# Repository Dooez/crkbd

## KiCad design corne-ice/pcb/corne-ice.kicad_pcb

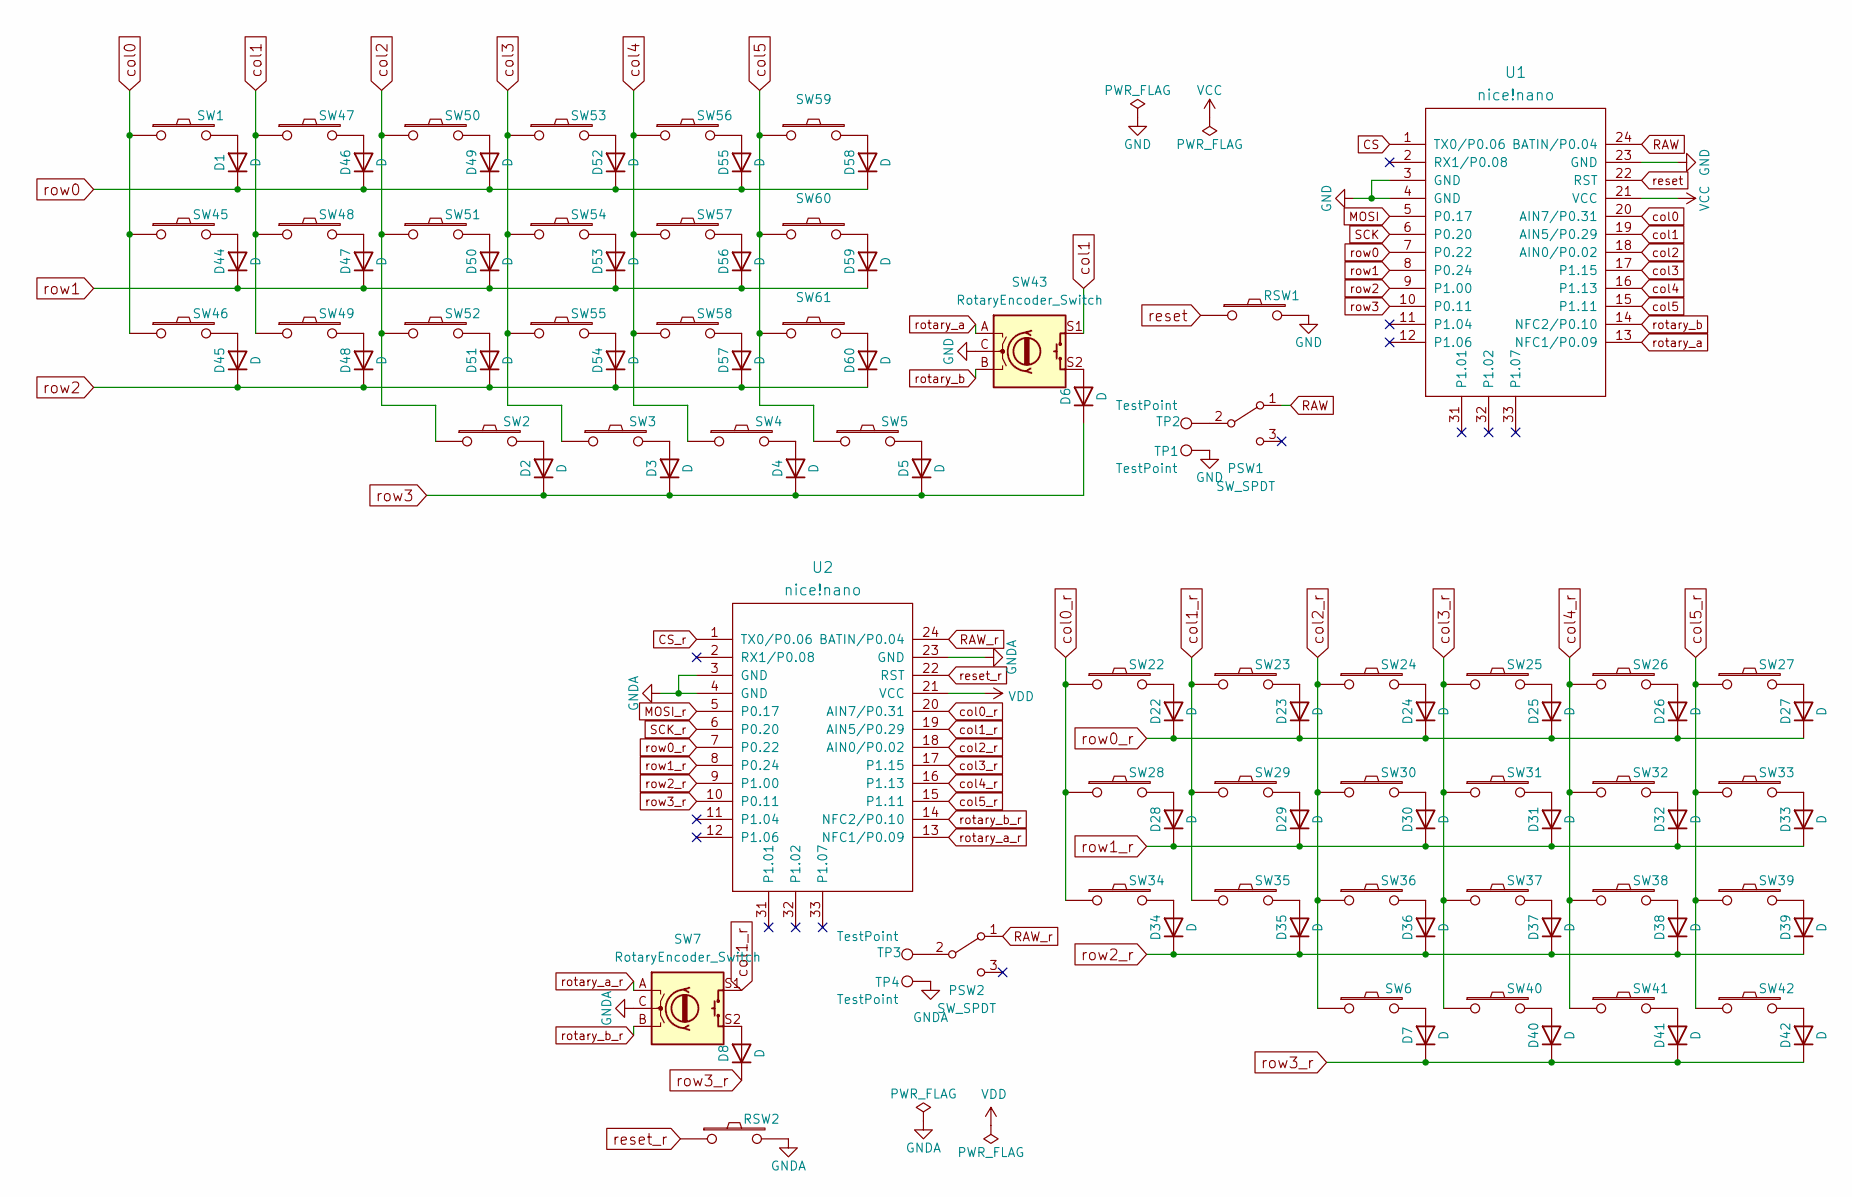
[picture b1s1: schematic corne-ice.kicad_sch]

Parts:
D1, D2, D3, D4, D5, D6, D7, D8, D22, D23, D24, D25, D26, D27, D28, D29, D30, D31, D32, D33, D34, D35, D36, D37, D38, D39, D40, D41, D42, D44, D45, D46, D47, D48, D49, D50, D51, D52, D53, D54, D55, D56, D57, D58, D59, D60: D; D3_SMD_v2
PSW1, PSW2: SW_SPDT; switch_SSSS811101
RSW1, RSW2: CPG151101S11-16; CherryMX_Hotswap
SW1, SW2, SW3, SW4, SW5, SW6, SW22, SW23, SW24, SW25, SW26, SW27, SW28, SW29, SW30, SW31, SW32, SW33, SW34, SW35, SW36, SW37, SW38, SW39, SW40, SW41, SW42, SW45, SW46, SW47, SW48, SW49, SW50, SW51, SW52, SW53, SW54, SW55, SW56, SW57, SW58, SW59, SW60, SW61: CPG151101S11-16; CherryMX_Hotswap
SW7, SW43: RotaryEncoder_Switch; RotaryEncoder_Alps_EC11E-Switch_Vertical_H20mm
TP1, TP4: TestPoint; TestPoint_Pad_1.5x1.5mm
TP2, TP3: TestPoint; TestPoint_Pad_D1.5mm
U1, U2: nice!nano; ProMicro_v3

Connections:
CS: U1.1 (TX0/P0.06)
CS_r: U2.1 (TX0/P0.06)
GND: RSW1.2, SW43.C, TP1.1, U1.3 (GND), U1.4 (GND), U1.23 (GND)
GNDA: RSW2.2, SW7.C, TP4.1, U2.3 (GND), U2.4 (GND), U2.23 (GND)
MOSI: U1.5 (P0.17)
MOSI_r: U2.5 (P0.17)
unnamed: D1.2 (A), SW1.2
unnamed: D2.2 (A), SW2.2
unnamed: D3.2 (A), SW3.2
unnamed: D4.2 (A), SW4.2
unnamed: D5.2 (A), SW5.2
unnamed: D6.2 (A), SW43.S2
unnamed: D7.2 (A), SW6.2
unnamed: D8.2 (A), SW7.S2
unnamed: D22.2 (A), SW22.2
unnamed: D23.2 (A), SW23.2
unnamed: D24.2 (A), SW24.2
unnamed: D25.2 (A), SW25.2
unnamed: D26.2 (A), SW26.2
unnamed: D27.2 (A), SW27.2
unnamed: D28.2 (A), SW28.2
unnamed: D29.2 (A), SW29.2
unnamed: D30.2 (A), SW30.2
unnamed: D31.2 (A), SW31.2
unnamed: D32.2 (A), SW32.2
unnamed: D33.2 (A), SW33.2
unnamed: D34.2 (A), SW34.2
unnamed: D35.2 (A), SW35.2
unnamed: D36.2 (A), SW36.2
unnamed: D37.2 (A), SW37.2
unnamed: D38.2 (A), SW38.2
unnamed: D39.2 (A), SW39.2
unnamed: D40.2 (A), SW40.2
unnamed: D41.2 (A), SW41.2
unnamed: D42.2 (A), SW42.2
unnamed: D44.2 (A), SW45.2
unnamed: D45.2 (A), SW46.2
unnamed: D46.2 (A), SW47.2
unnamed: D47.2 (A), SW48.2
unnamed: D48.2 (A), SW49.2
unnamed: D49.2 (A), SW50.2
unnamed: D50.2 (A), SW51.2
unnamed: D51.2 (A), SW52.2
unnamed: D52.2 (A), SW53.2
unnamed: D53.2 (A), SW54.2
unnamed: D54.2 (A), SW55.2
unnamed: D55.2 (A), SW56.2
unnamed: D56.2 (A), SW57.2
unnamed: D57.2 (A), SW58.2
unnamed: D58.2 (A), SW59.2
unnamed: D59.2 (A), SW60.2
unnamed: D60.2 (A), SW61.2
unnamed: PSW1.2 (B), TP2.1
unnamed: PSW2.2 (B), TP3.1
RAW: PSW1.1 (A), U1.24 (BATIN/P0.04)
RAW_r: PSW2.1 (A), U2.24 (BATIN/P0.04)
SCK: U1.6 (P0.20)
SCK_r: U2.6 (P0.20)
VCC: U1.21 (VCC)
VDD: U2.21 (VCC)
col0: SW1.1, SW45.1, SW46.1, U1.20 (AIN7/P0.31)
col0_r: SW22.1, SW28.1, SW34.1, U2.20 (AIN7/P0.31)
col1: SW43.S1, SW47.1, SW48.1, SW49.1, U1.19 (AIN5/P0.29)
col1_r: SW7.S1, SW23.1, SW29.1, SW35.1, U2.19 (AIN5/P0.29)
col2: SW2.1, SW50.1, SW51.1, SW52.1, U1.18 (AIN0/P0.02)
col2_r: SW6.1, SW24.1, SW30.1, SW36.1, U2.18 (AIN0/P0.02)
col3: SW3.1, SW53.1, SW54.1, SW55.1, U1.17 (P1.15)
col3_r: SW25.1, SW31.1, SW37.1, SW40.1, U2.17 (P1.15)
col4: SW4.1, SW56.1, SW57.1, SW58.1, U1.16 (P1.13)
col4_r: SW26.1, SW32.1, SW38.1, SW41.1, U2.16 (P1.13)
col5: SW5.1, SW59.1, SW60.1, SW61.1, U1.15 (P1.11)
col5_r: SW27.1, SW33.1, SW39.1, SW42.1, U2.15 (P1.11)
reset: RSW1.1, U1.22 (RST)
reset_r: RSW2.1, U2.22 (RST)
rotary_a: SW43.A, U1.13 (NFC1/P0.09)
rotary_a_r: SW7.A, U2.13 (NFC1/P0.09)
rotary_b: SW43.B, U1.14 (NFC2/P0.10)
rotary_b_r: SW7.B, U2.14 (NFC2/P0.10)
row0: D1.1 (K), D46.1 (K), D49.1 (K), D52.1 (K), D55.1 (K), D58.1 (K), U1.7 (P0.22)
row0_r: D22.1 (K), D23.1 (K), D24.1 (K), D25.1 (K), D26.1 (K), D27.1 (K), U2.7 (P0.22)
row1: D44.1 (K), D47.1 (K), D50.1 (K), D53.1 (K), D56.1 (K), D59.1 (K), U1.8 (P0.24)
row1_r: D28.1 (K), D29.1 (K), D30.1 (K), D31.1 (K), D32.1 (K), D33.1 (K), U2.8 (P0.24)
row2: D45.1 (K), D48.1 (K), D51.1 (K), D54.1 (K), D57.1 (K), D60.1 (K), U1.9 (P1.00)
row2_r: D34.1 (K), D35.1 (K), D36.1 (K), D37.1 (K), D38.1 (K), D39.1 (K), U2.9 (P1.00)
row3: D2.1 (K), D3.1 (K), D4.1 (K), D5.1 (K), D6.1 (K), U1.10 (P0.11)
row3_r: D7.1 (K), D8.1 (K), D40.1 (K), D41.1 (K), D42.1 (K), U2.10 (P0.11)

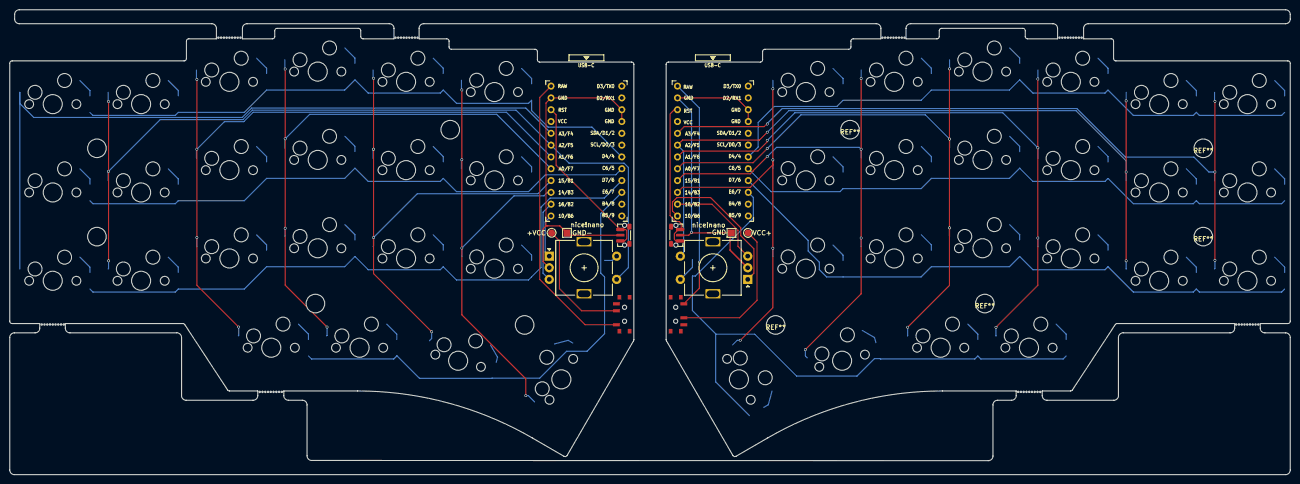
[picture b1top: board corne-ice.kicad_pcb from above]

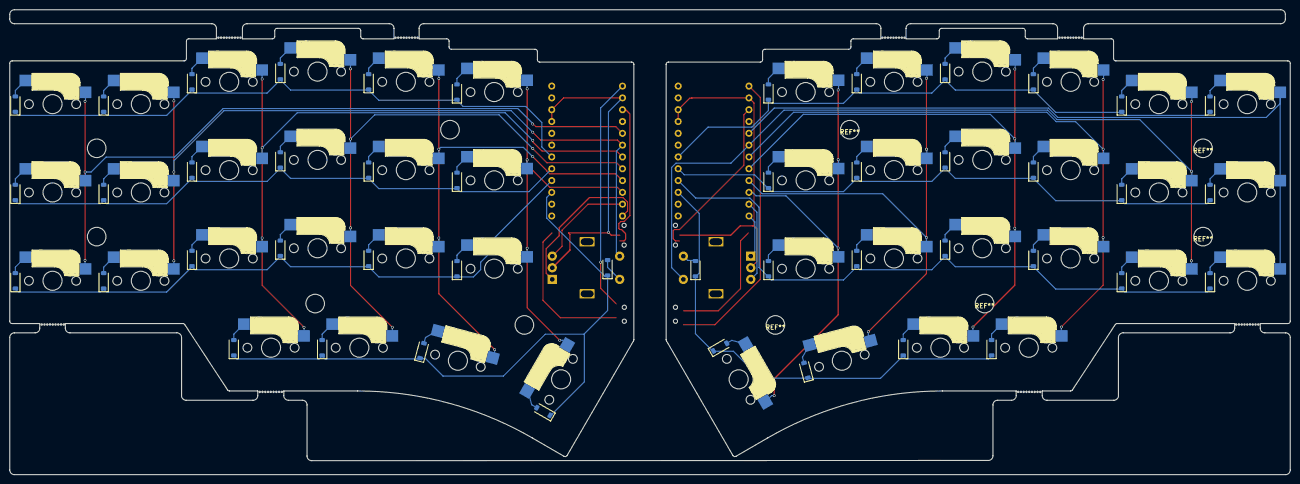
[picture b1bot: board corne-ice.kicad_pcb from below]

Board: 2 copper layers, 275.4 x 100.0 mm, 102 parts (46 on the bottom side), 78 nets.

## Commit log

2023-10-27 Added a button and rotary encoder.
2023-10-28 Left part updated
2023-10-28 Right half
2023-10-28 Smoothed outline and added holes.
2023-10-28 Backup.
2023-10-29 Ordered.
2023-11-22 Fixes missing via.
